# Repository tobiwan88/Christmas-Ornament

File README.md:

# TREE-01 — Wireless RGB Christmas Tree Ornament

**TREE-01** is a double-sided, battery-powered Bluetooth LE Christmas tree ornament built from two stacked 4-layer matte-black & ENIG-gold PCBs. Designed in KiCad 10 with automated geometry, DRC, EMI, and BOM/fab verification.

---

## Highlights

- **Double-Sided 16-LED RGB Matrix:** 16× tiny `1.0 × 1.0 mm` common-anode RGB LEDs (`XL-1010RGB-YG`) — 8 on the front (Board B) and 8 mirrored on the back (Board A) — charlieplexed across just 8 GPIO lines with ghost-free slot scheduling.
- **Ultra-Low-Power BLE SoC:** Nordic `nRF54L10` (QFN-48, pin-compatible with `nRF54L15`) with a `2.45 GHz` Johanson chip antenna at the copper-free tree tip for phone-based time sync, effect selection, and BLE DFU.
- **Smart Power Architecture:** `TPS63900` buck-boost regulator switches between **3.0 V** in sleep (`< 5 µA` whole-board target) and **3.5 V** while LEDs are lit, delivering **~36 days** of runtime (11 h/day schedule) on 2× AAA alkaline cells.
- **Two Power Variants, One PCB:**
  - **Variant A (default):** JLC-assembled SMT 2× AAA holder (`BH-AAA-B5AA001`) centered in the 12 mm inter-board gap.
  - **Variant B:** Rechargeable Li-ion pouch cell with `MCP73831` charger and USB-C power input.
- **Clean 12 mm Sandwich Stack:** Two 1.0 mm boards joined by a single mated 2×4 `2.54 mm` SMD header (8 LED lines) and two `12.0 mm` M2 brass hex standoffs (carrying GND to Board B) with black nylon screws.

---

## Specifications

| Parameter | Value |
|---|---|
| **Dimensions** | `70 × 105 mm` outline, `14.0 mm` board-to-board (`14.8 mm` over LEDs) |
| **PCB Stackup** | 4-layer, `1.0 mm` (`JLC04101H-7628`), matte black solder mask, ENIG gold |
| **MCU & RF** | `nRF54L10-QFAA` (BLE 2.4 GHz), Johanson `2450AT42A100E` chip antenna |
| **LEDs** | 16× `XL-1010RGB-YG` (`1 × 1 × 0.4 mm`), 48 dies charlieplexed on 8 lines |
| **Power** | `TPS63900` buck-boost (`3.0 V` idle / `3.5 V` lit), reverse-polarity P-FET (`Q1`) |
| **Battery** | Variant A: 2× AAA in series (`~36 days` @ 1.0 mA default) · Variant B: Li-ion + USB-C |
| **Controls & Debug** | Rear tactile switch `SW1` (wake / effect / pair), Tag-Connect `TC2030-NL` SWD pads |
| **Panelization** | Single customer panel (`114.8 × 120.0 mm`) nesting Board A and Board B |

---

## Render Gallery

| Front (Board B) | 3/4 View (Inner Board A & Traces) |
|---|---|
|  |  |

| Side Stack (12 mm Gap, AAA Cells & Header) | Back (Board A, SW1 & Tag-Connect) |
|---|---|
|  |  |

---

## Repository Structure

- [`hardware/tree-a/`](hardware/tree-a/) — Main board (SoC, RF, power, battery holder / charger, `D9–D16`, `SW1`, `TC1`)
- [`hardware/tree-b/`](hardware/tree-b/) — Front LED board (`D1–D8`, mated male header `J4`, solid inner GND planes)
- [`hardware/panel/`](hardware/panel/) — Nested 2-board customer panel and [MECHANICAL.md](hardware/panel/MECHANICAL.md)
- [`hardware/ARCHITECTURE.md`](hardware/ARCHITECTURE.md) — Pin plan, charlieplex matrix, and board-to-board interface
- [`hardware/REQUIREMENTS.md`](hardware/REQUIREMENTS.md) — System requirements, power budget, and fab limits
- [`hardware/DECISIONS.md`](hardware/DECISIONS.md) — Engineering decision log (`D1–D37`)
- [`design/`](design/) — V3 design mockups and 3D renders
- [`scripts/`](scripts/) — Automated KiCad DRC, geometry, RF impedance, and BOM/fab verification hooks

---

## License

See [LICENSE](LICENSE).

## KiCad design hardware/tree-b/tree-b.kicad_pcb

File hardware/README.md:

# Hardware: where to look

One row per board. Keep this file current; CLAUDE.md points here instead of naming boards.

| Board | Status | Gate | Notes |
|---|---|---|---|
| tree-a | schematic built and reviewed (3 rounds); routed and frozen, DRC 0 / 0 / 0, parity 0, known exceptions D35 | 5 built; 6 package built, order open | hardware/tree-a/BOARD.md (Routing, Routing review), PARTS-REVIEW.md; owns the order fees |
| tree-b | schematic built and reviewed; routed with KiCadRoutingTools (D31 ground via standoffs), DRC 0 / 0 / 0 | 5 built; 6 via the panel | hardware/tree-b/BOARD.md; fees are paid by tree-a |
| panel | built by gen/panel_pcb.py (114.8 x 120.0 mm, 8 mouse-bite tabs, rails, fiducials), panel-own DRC 0; fab package built (hardware/out/fab/panel) | 6 package built, order open | hardware/panel/BOARD.md, MECHANICAL.md, ORDER.md |

Project documents: REQUIREMENTS.md, ARCHITECTURE.md, DECISIONS.md (D1-D36), NOTES-routing-lessons.md, GATES.md, REVIEW-2026-11-23.md, RESEARCH-2026-11-23.md,
FIRMWARE-RULES.md, ORDER.md (manual PCB + shipping quote, bring-up list). The template board `ornamnents` was retired.

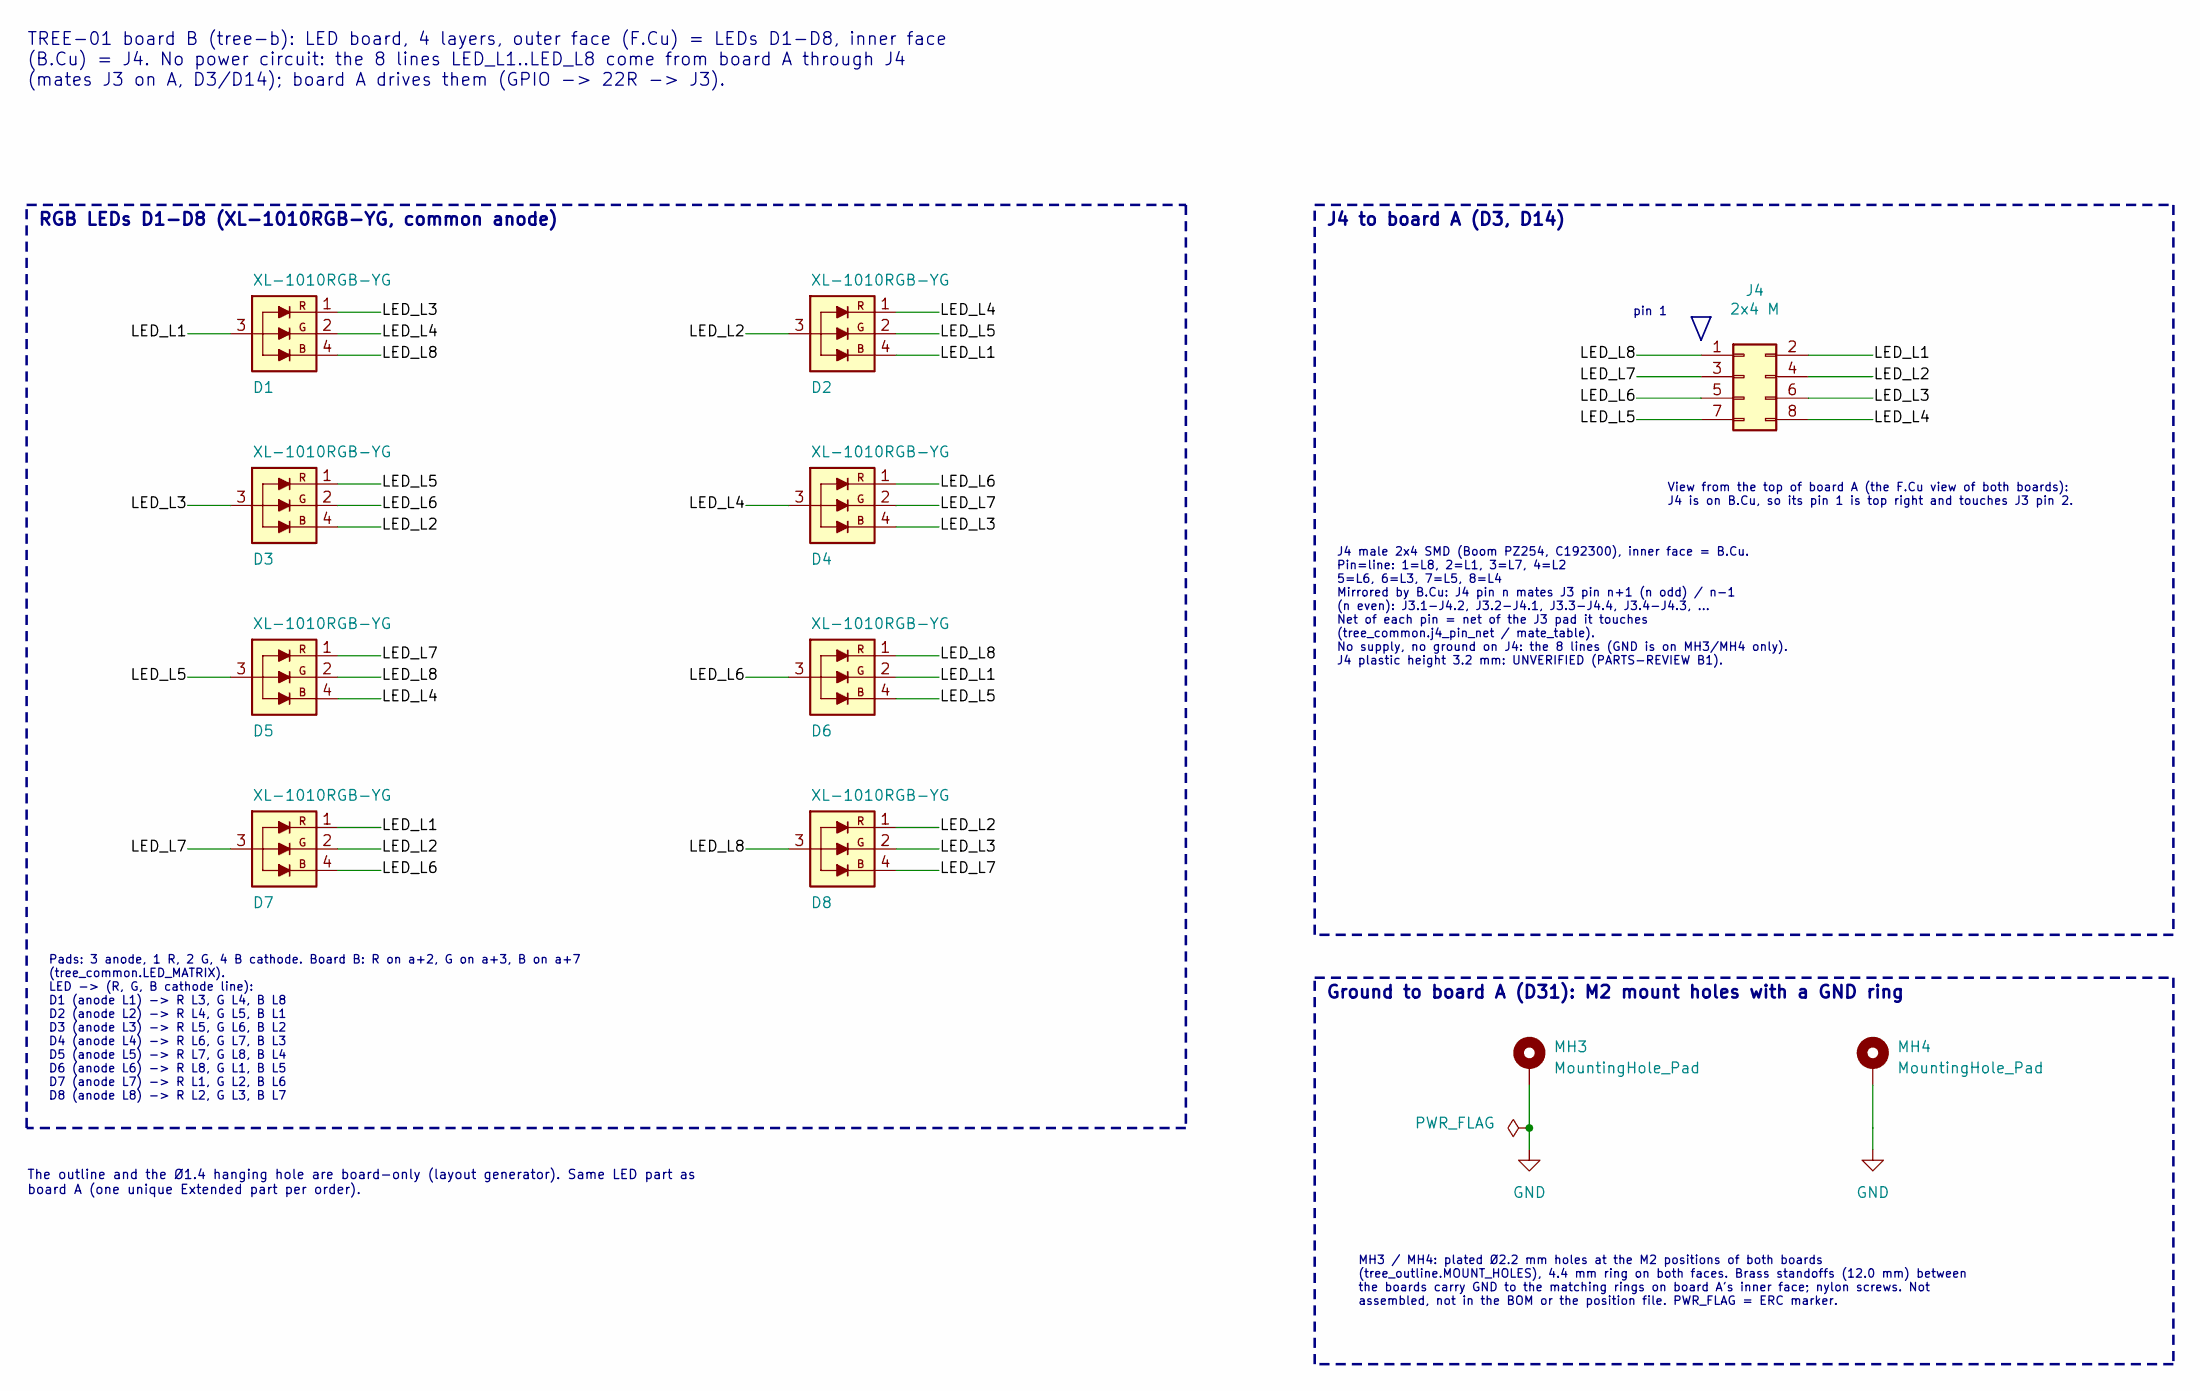
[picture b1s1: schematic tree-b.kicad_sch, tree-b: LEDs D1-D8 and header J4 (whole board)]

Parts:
D1, D2, D3, D4, D5, D6, D7, D8: XL-1010RGB-YG; LED_XL-1010RGB-YG; LCSC C965834
J4: 2x4 M; PinHeader_2x04_SMD_Boom_PZ254; LCSC C192300
MH3, MH4: MountingHole_Pad; MountingHole_2.2mm_M2_Pad

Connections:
/LED_L1: D1.3 (A), D2.4 (BK), D6.2 (GK), D7.1 (RK), J4.2
/LED_L2: D2.3 (A), D3.4 (BK), D7.2 (GK), D8.1 (RK), J4.4
/LED_L3: D1.1 (RK), D3.3 (A), D4.4 (BK), D8.2 (GK), J4.6
/LED_L4: D1.2 (GK), D2.1 (RK), D4.3 (A), D5.4 (BK), J4.8
/LED_L5: D2.2 (GK), D3.1 (RK), D5.3 (A), D6.4 (BK), J4.7
/LED_L6: D3.2 (GK), D4.1 (RK), D6.3 (A), D7.4 (BK), J4.5
/LED_L7: D4.2 (GK), D5.1 (RK), D7.3 (A), D8.4 (BK), J4.3
/LED_L8: D1.4 (BK), D5.2 (GK), D6.1 (RK), D8.3 (A), J4.1
GND: MH3.1, MH4.1

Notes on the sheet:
TREE-01 board B (tree-b): LED board, 4 layers, outer face (F.Cu) = LEDs D1-D8, inner face (B.Cu) = J4. No power circuit: the 8 lines LED_L1..LED_L8 come from board A through J4 (mates J3 on A, D3/D14); board A drives them (GPIO -> 22R -> J3).
Pads: 3 anode, 1 R, 2 G, 4 B cathode. Board B: R on a+2, G on a+3, B on a+7 (tree_common.LED_MATRIX). LED -> (R, G, B cathode line): D1 (anode L1) -> R L3, G L4, B L8 D2 (anode L2) -> R L4, G L5, B L1 D3 (anode L3) -> R L5, G L6, B L2 D4 (anode L4) -> R L6, G L7, B L3 D5 (anode L5) -> R L7, G L8, B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
The outline and the Ø1.4 hanging hole are board-only (layout generator). Same LED part as board A (one unique Extended part per order).
RGB LEDs D1-D8 (XL-1010RGB-YG, common anode)
J4 to board A (D3, D14)
MH3 / MH4: plated Ø2.2 mm holes at the M2 positions of both boards (tree_outline.MOUNT_HOLES), 4.4 mm ring on both faces. Brass standoffs (12.0 mm) between the boards carry GND to the matching rings on board A's inner face; nylon screws. Not assembled, not in the BOM or the position file. PWR_FLAG 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
View from the top of board A (the F.Cu view of both boards): J4 is on B.Cu, so its pin 1 is top right and touches J3 pin 2.
Ground to board A (D31): M2 mount holes with a GND ring
pin 1
J4 male 2x4 SMD (Boom PZ254, C192300), inner face = B.Cu. Pin=line: 1=L8, 2=L1, 3=L7, 4=L2 5=L6, 6=L3, 7=L5, 8=L4 Mirrored by B.Cu: J4 pin n mates J3 pin n+1 (n odd) / n-1 (n even): J3.1-J4.2, J3.2-J4.1, J3.3-J4.4, J3.4-J4.3, ... Net of each pin = net of the J3 pad it touches (tree_common.j4_pin_ne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

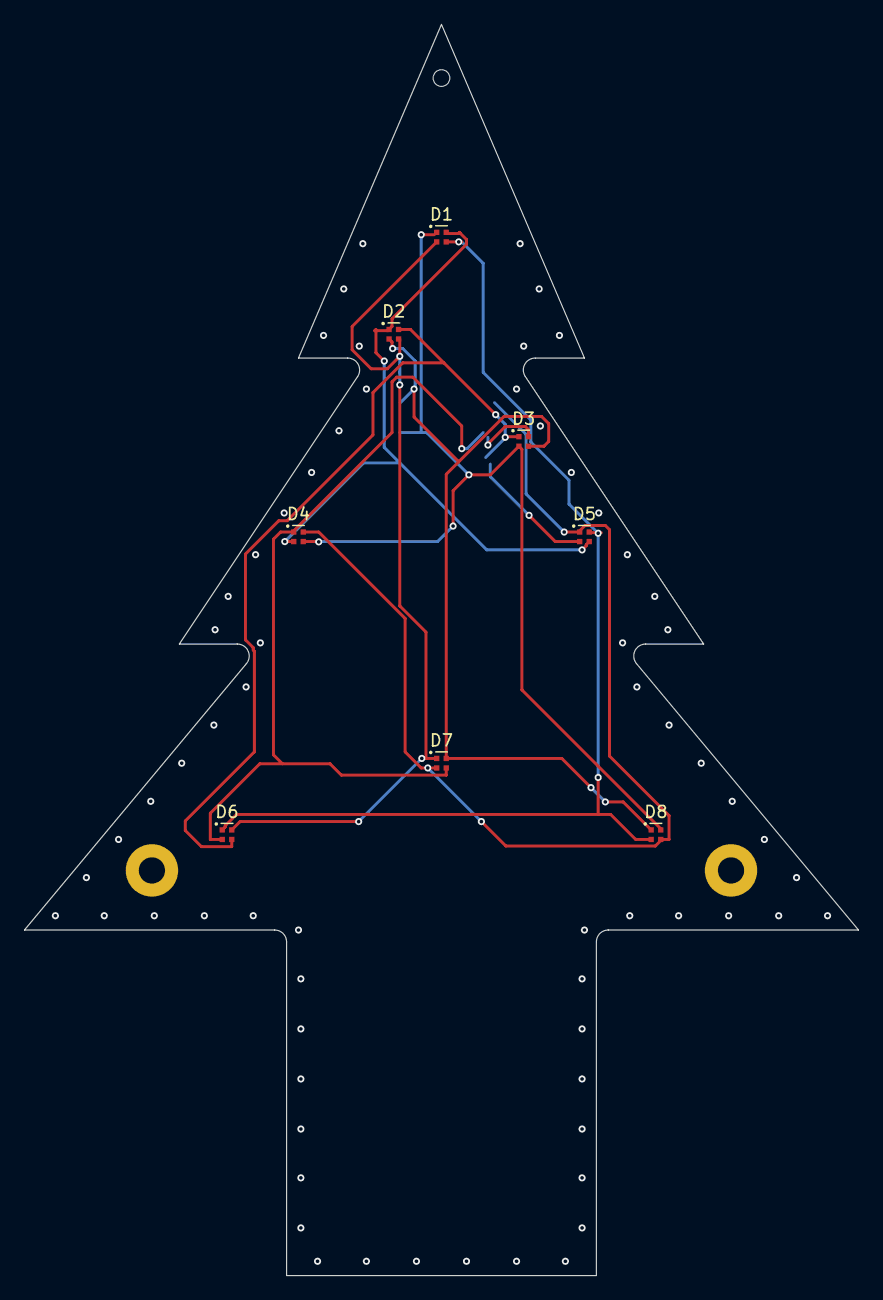
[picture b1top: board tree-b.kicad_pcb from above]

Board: 4 copper layers, 70.0 x 105.0 mm, 12 parts (1 on the bottom side), 9 nets.

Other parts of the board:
H_HANG: NPTH 1.4; MountingHole_1.4mm

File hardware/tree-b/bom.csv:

Comment,Designator,Footprint,Quantity,LCSC Part #,Class,Status,Function / notes
XL-1010RGB-YG (1010),"D1,D2,D3,D4,D5,D6,D7,D8",LED_XL-1010RGB-YG,8,C965834,Extended,"datasheet card, stock 2026-11-23 (PARTS-REVIEW)","RGB LED, outer face (F.Cu of board B)"
2.54-2x4 vertical SMD pin (SMD 2x4 2.54),J4,PinHeader_2x04_SMD_Boom_PZ254,1,C192300,Extended,"datasheet card, stock 2026-11-23 (PARTS-REVIEW)","male header to board A (D3), inner face (B.Cu); mates J3 by position (D14)"

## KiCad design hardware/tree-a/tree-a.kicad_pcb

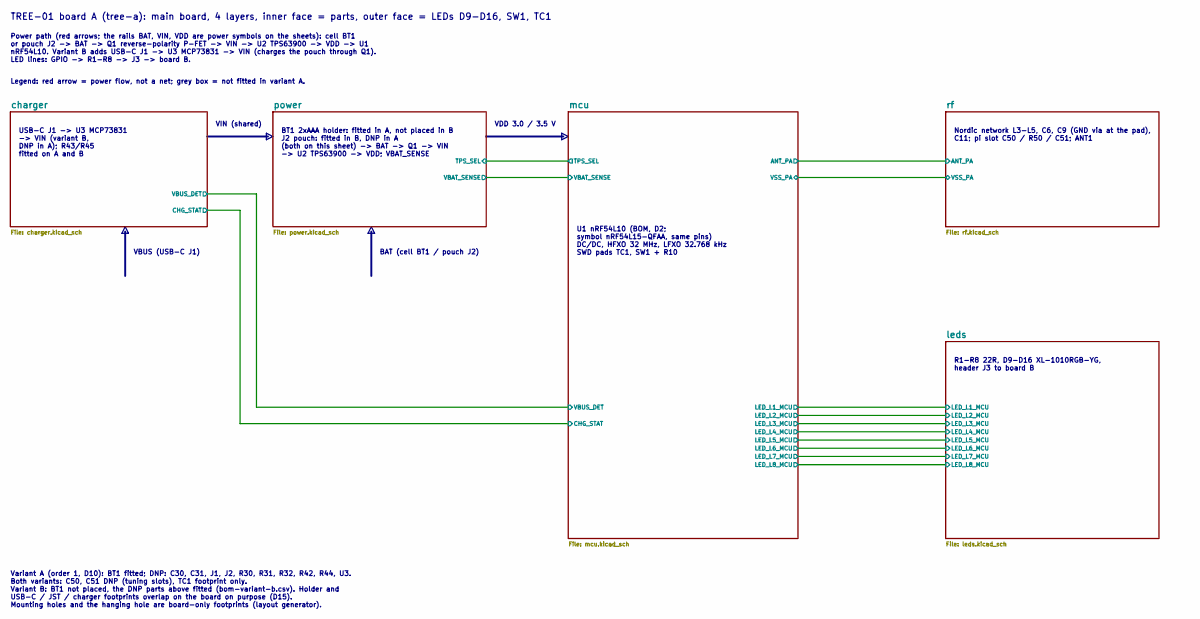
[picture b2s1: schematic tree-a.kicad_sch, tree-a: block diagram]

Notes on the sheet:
BT1 2xAAA holder: fitted in A, not placed in B J2 pouch: fitted in B, DNP in A (both on this sheet) -> BAT -> Q1 -> VIN -> U2 TPS63900 -> VDD; VBAT_SENSE
VBUS (USB-C J1)
VDD 3.0 / 3.5 V
TREE-01 board A (tree-a): main board, 4 layers, inner face = parts, outer face = LEDs D9-D16, SW1, TC1
BAT (cell BT1 / pouch J2)
VIN (shared)
Nordic network L3-L5, C6, C9 (GND via at the pad), C11; pi slot C50 / R50 / C51; ANT1
Variant A (order 1, D10): BT1 fitted; DNP: C30, C31, J1, J2, R30, R31, R32, R42, R44, U3. Both variants: C50, C51 DNP (tuning slots), TC1 footprint only. Variant B: BT1 not placed, the DNP parts above fitted (bom-variant-b.csv). Holder and USB-C / JST / charger footprints overlap on the board on pu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
USB-C J1 -> U3 MCP73831 -> VIN (variant B, DNP in A); R43/R45 fitted on A and B
U1 nRF54L10 (BOM, D2; symbol nRF54L15-QFAA, same pins) DC/DC, HFXO 32 MHz, LFXO 32.768 kHz SWD pads TC1, SW1 + R10
Power path (red arrows; the rails BAT, VIN, VDD are power symbols on the sheets): cell BT1 or pouch J2 -> BAT -> Q1 reverse-polarity P-FET -> VIN -> U2 TPS63900 -> VDD -> U1 nRF54L10. Variant B adds USB-C J1 -> U3 MCP73831 -> VIN (charges the pouch through Q1). LED lines: GPIO -> R1-R8 -> J3 -> boa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
R1-R8 22R, D9-D16 XL-1010RGB-YG, header J3 to board B
Legend: red arrow = power flow, not a net; grey box = not fitted in variant A.

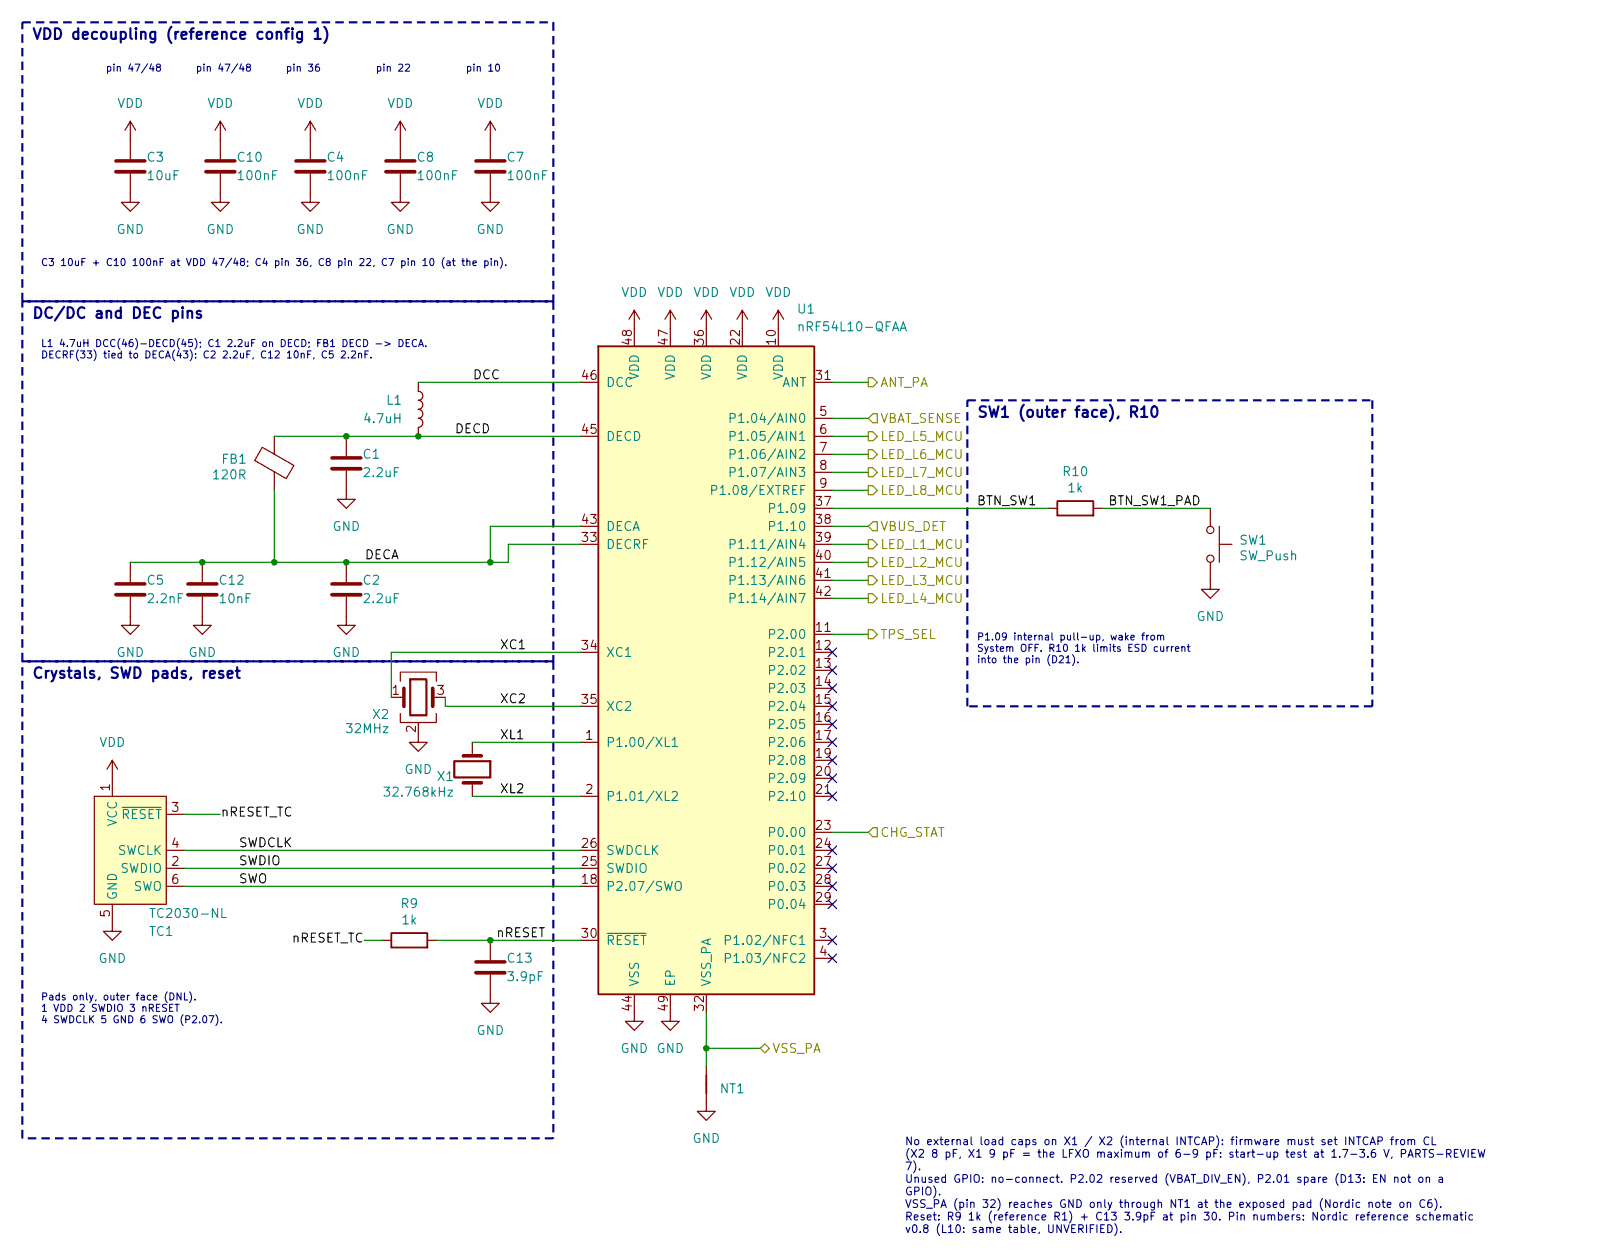
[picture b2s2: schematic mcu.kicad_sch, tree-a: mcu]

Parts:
C1, C2: 2.2uF; C_0402_1005Metric; LCSC C12530
C3: 10uF; C_0402_1005Metric; LCSC C15525
C4, C7, C8, C10: 100nF; C_0402_1005Metric; LCSC C1525
C5: 2.2nF; C_0402_1005Metric; LCSC C1531
C12: 10nF; C_0402_1005Metric; LCSC C15195
C13: 3.9pF; C_0402_1005Metric; LCSC C313081
FB1: 120R; L_0402_1005Metric; LCSC C38480
L1: 4.7uH; L_0805_2012Metric; LCSC C63166
NT1: NetTie; NetTie-2_SMD_Bridge0.2mm
R9, R10: 1k; R_0402_1005Metric; LCSC C11702
SW1: SW_Push; SW_HX_3x4x2-2P-1.6N; LCSC C49234124
TC1: TC2030-NL; Tag-Connect_TC2030-IDC-NL_2x03_P1.27mm_Vertical
U1: nRF54L10-QFAA; QFN-48-1EP_6x6mm_P0.4mm_EP4.66x4.66mm_ThermalVias; LCSC C44800139
X1: 32.768kHz; Crystal_SMD_2012-2Pin_2.0x1.2mm; LCSC C510776
X2: 32MHz; Crystal_SMD_2016-4Pin_2.0x1.6mm; LCSC C2965582

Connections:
/charger/CHG_STAT: U1.23 (P0.00); also elsewhere on the board
/charger/VBUS_DET: U1.38 (P1.10); also elsewhere on the board
/leds/LED_L1_MCU: U1.39 (P1.11/AIN4); also elsewhere on the board
/leds/LED_L2_MCU: U1.40 (P1.12/AIN5); also elsewhere on the board
/leds/LED_L3_MCU: U1.41 (P1.13/AIN6); also elsewhere on the board
/leds/LED_L4_MCU: U1.42 (P1.14/AIN7); also elsewhere on the board
/leds/LED_L5_MCU: U1.6 (P1.05/AIN1); also elsewhere on the board
/leds/LED_L6_MCU: U1.7 (P1.06/AIN2); also elsewhere on the board
/leds/LED_L7_MCU: U1.8 (P1.07/AIN3); also elsewhere on the board
/leds/LED_L8_MCU: U1.9 (P1.08/EXTREF); also elsewhere on the board
/mcu/ANT_PA: U1.31 (ANT); also elsewhere on the board
/mcu/BTN_SW1: R10.1, U1.37 (P1.09)
/mcu/BTN_SW1_PAD: R10.2, SW1.1
/mcu/DCC: L1.1, U1.46 (DCC)
/mcu/DECA: C2.1, C5.1, C12.1, FB1.2, U1.33 (DECRF), U1.43 (DECA)
/mcu/DECD: C1.1, FB1.1, L1.2, U1.45 (DECD)
/mcu/SWDCLK: TC1.4 (SWCLK), U1.26 (SWDCLK)
/mcu/SWDIO: TC1.2 (SWDIO), U1.25 (SWDIO)
/mcu/SWO: TC1.6 (SWO), U1.18 (P2.07/SWO)
/mcu/TPS_SEL: U1.11 (P2.00); also elsewhere on the board
/mcu/VBAT_SENSE: U1.5 (P1.04/AIN0); also elsewhere on the board
/mcu/VSS_PA: NT1.1, U1.32 (VSS_PA); also elsewhere on the board
/mcu/XC1: U1.34 (XC1), X2.1
/mcu/XC2: U1.35 (XC2), X2.3
/mcu/XL1: U1.1 (P1.00/XL1), X1.1
/mcu/XL2: U1.2 (P1.01/XL2), X1.2
/mcu/nRESET: C13.1, R9.2, U1.30 (~RESET)
/mcu/nRESET_TC: R9.1, TC1.3 (~RESET)
GND: C1.2, C2.2, C3.2, C4.2, C5.2, C7.2, C8.2, C10.2, C12.2, C13.2, NT1.2, SW1.2, TC1.5 (GND), U1.44 (VSS), U1.49 (EP), X2.2 (G), X2.4 (G); also elsewhere on the board
VDD: C3.1, C4.1, C7.1, C8.1, C10.1, TC1.1 (VCC), U1.10 (VDD), U1.22 (VDD), U1.36 (VDD), U1.47 (VDD), U1.48 (VDD); also elsewhere on the board

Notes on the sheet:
DC/DC and DEC pins
pin 47/48
Crystals, SWD pads, reset
P1.09 internal pull-up, wake from System OFF. R10 1k limits ESD current into the pin (D21).
L1 4.7uH DCC(46)-DECD(45); C1 2.2uF on DECD; FB1 DECD -> DECA. DECRF(33) tied to DECA(43): C2 2.2uF, C12 10nF, C5 2.2nF.
pin 36
VDD decoupling (reference config 1)
C3 10uF + C10 100nF at VDD 47/48; C4 pin 36, C8 pin 22, C7 pin 10 (at the pin).
pin 22
No external load caps on X1 / X2 (internal INTCAP): firmware must set INTCAP from CL (X2 8 pF, X1 9 pF = the LFXO maximum of 6-9 pF: start-up test at 1.7-3.6 V, PARTS-REVIEW 7). Unused GPIO: no-connect. P2.02 reserved (VBAT_DIV_EN), P2.01 spare (D13: EN not on a GPIO). VSS_PA (pin 32) reaches GND o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
pin 10
Pads only, outer face (DNL). 1 VDD 2 SWDIO 3 nRESET 4 SWDCLK 5 GND 6 SWO (P2.07).
SW1 (outer face), R10

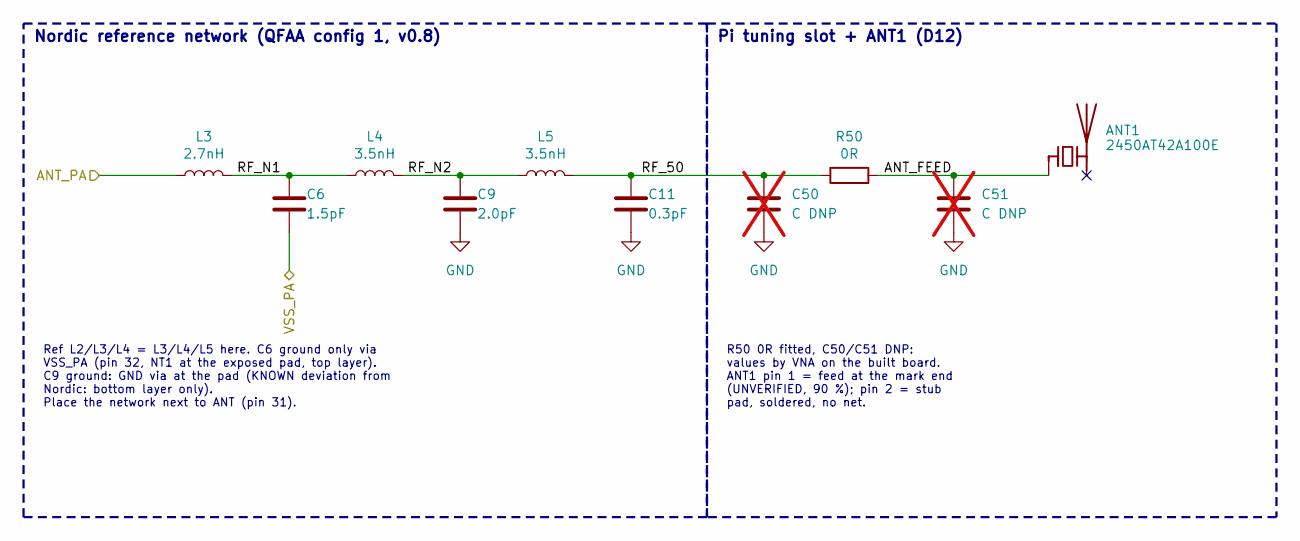
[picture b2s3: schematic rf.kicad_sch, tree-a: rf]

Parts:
ANT1: 2450AT42A100E; ANT_Johanson_2450AT42A100E; LCSC C2917719
C6: 1.5pF; C_0201_0603Metric; LCSC C435397
C9: 2.0pF; C_0201_0603Metric; LCSC C668326
C11: 0.3pF; C_0201_0603Metric; LCSC C161289
C50, C51: C DNP; C_0402_1005Metric; not fitted
L3: 2.7nH; L_0201_0603Metric; LCSC C7216765
L4, L5: 3.5nH; L_0201_0603Metric; LCSC C3911055
R50: 0R; R_0402_1005Metric; LCSC C17168

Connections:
/mcu/ANT_PA: L3.1; also elsewhere on the board
/mcu/VSS_PA: C6.2; also elsewhere on the board
/rf/ANT_FEED: ANT1.1 (FEED), C51.1, R50.2
/rf/RF_50: C11.1, C50.1, L5.2, R50.1
/rf/RF_N1: C6.1, L3.2, L4.1
/rf/RF_N2: C9.1, L4.2, L5.1
GND: C9.2, C11.2, C50.2, C51.2; also elsewhere on the board

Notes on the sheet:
Pi tuning slot + ANT1 (D12)
Ref L2/L3/L4 = L3/L4/L5 here. C6 ground only via VSS_PA (pin 32, NT1 at the exposed pad, top layer). C9 ground: GND via at the pad (KNOWN deviation from Nordic: bottom layer only). Place the network next to ANT (pin 31).
Nordic reference network (QFAA config 1, v0.8)
R50 0R fitted, C50/C51 DNP: values by VNA on the built board. ANT1 pin 1 = feed at the mark end (UNVERIFIED, 90 %); pin 2 = stub pad, soldered, no net.

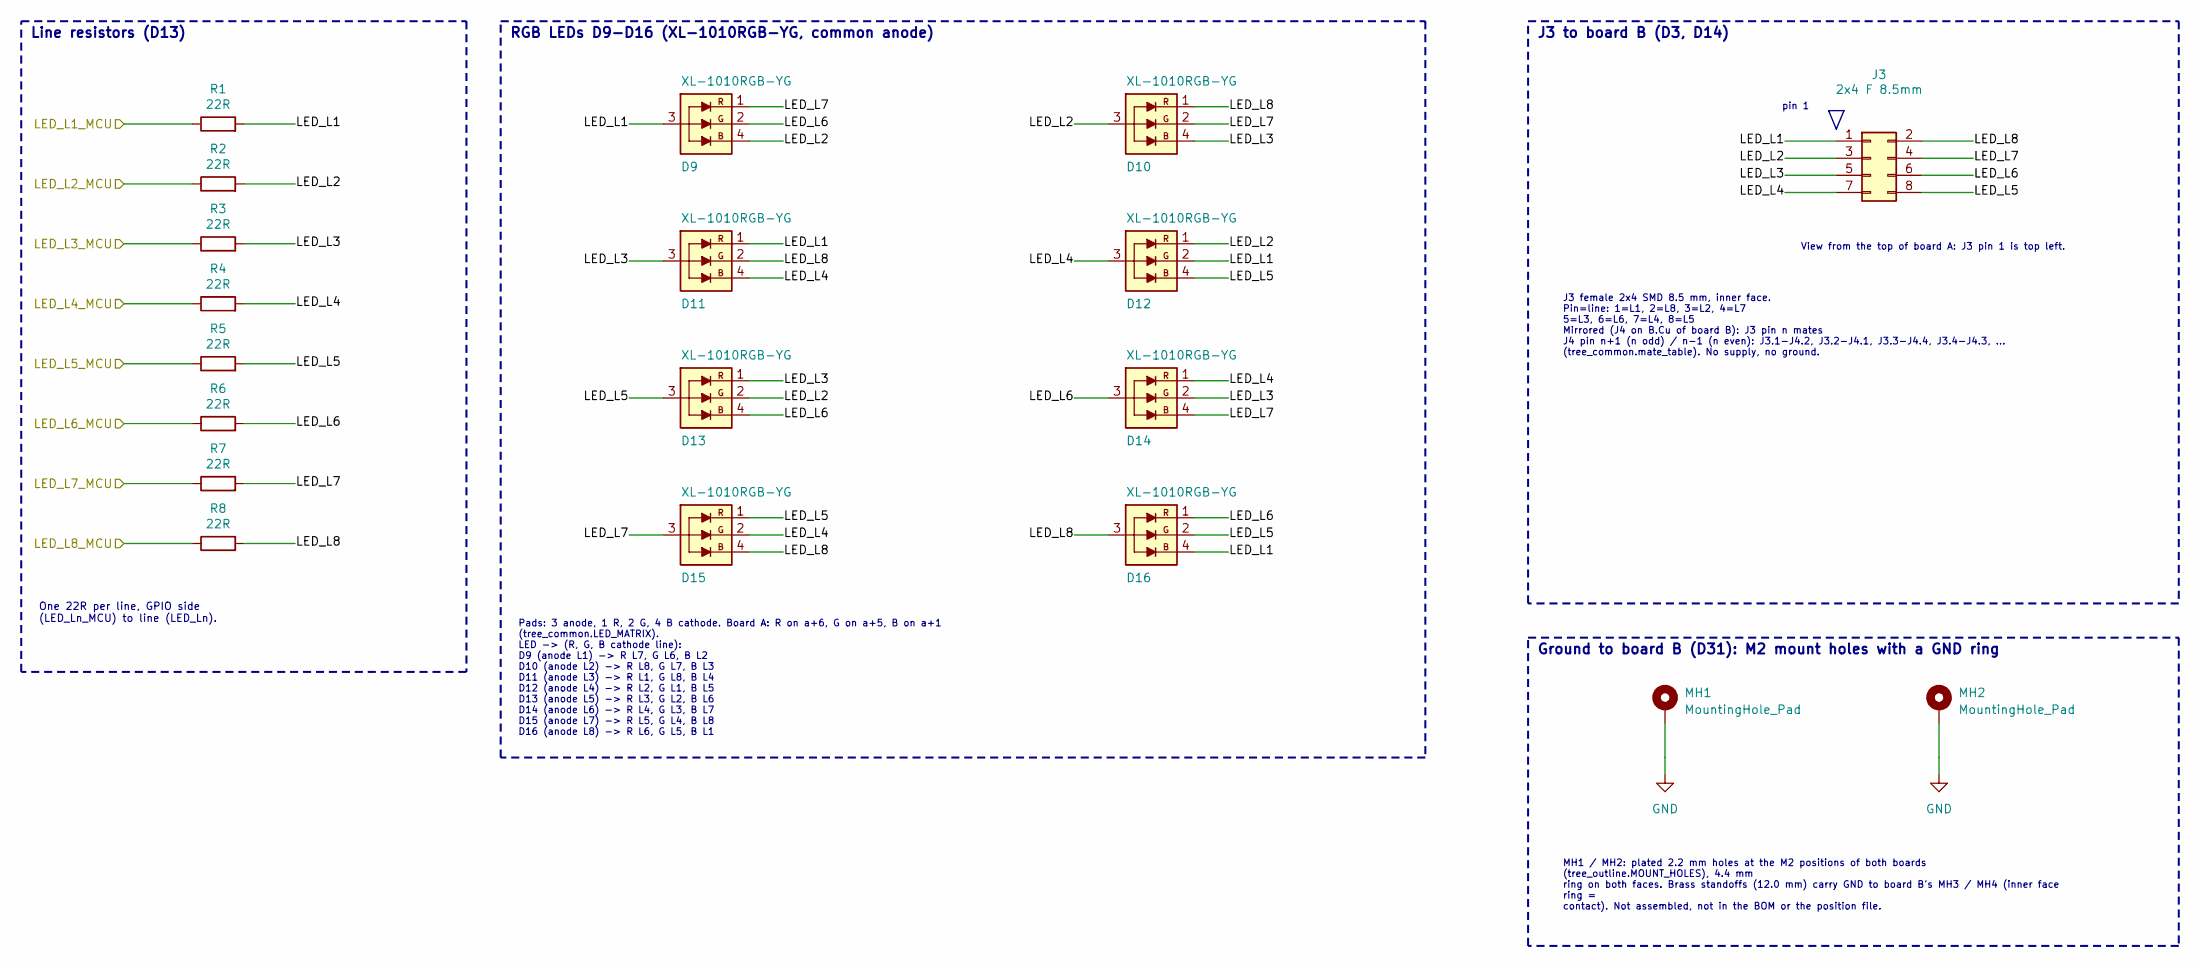
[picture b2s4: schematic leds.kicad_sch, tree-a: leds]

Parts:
D9, D10, D11, D12, D13, D14, D15, D16: XL-1010RGB-YG; LED_XL-1010RGB-YG; LCSC C965834
J3: 2x4 F 8.5mm; PinSocket_2x04_SMD_HC-PM254-8.5H; LCSC C22373945
MH1, MH2: MountingHole_Pad; MountingHole_2.2mm_M2_Pad
R1, R2, R3, R4, R5, R6, R7, R8: 22R; R_0402_1005Metric; LCSC C25092

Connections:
/leds/LED_L1: D9.3 (A), D11.1 (RK), D12.2 (GK), D16.4 (BK), J3.1, R1.2
/leds/LED_L1_MCU: R1.1; also elsewhere on the board
/leds/LED_L2: D9.4 (BK), D10.3 (A), D12.1 (RK), D13.2 (GK), J3.3, R2.2
/leds/LED_L2_MCU: R2.1; also elsewhere on the board
/leds/LED_L3: D10.4 (BK), D11.3 (A), D13.1 (RK), D14.2 (GK), J3.5, R3.2
/leds/LED_L3_MCU: R3.1; also elsewhere on the board
/leds/LED_L4: D11.4 (BK), D12.3 (A), D14.1 (RK), D15.2 (GK), J3.7, R4.2
/leds/LED_L4_MCU: R4.1; also elsewhere on the board
/leds/LED_L5: D12.4 (BK), D13.3 (A), D15.1 (RK), D16.2 (GK), J3.8, R5.2
/leds/LED_L5_MCU: R5.1; also elsewhere on the board
/leds/LED_L6: D9.2 (GK), D13.4 (BK), D14.3 (A), D16.1 (RK), J3.6, R6.2
/leds/LED_L6_MCU: R6.1; also elsewhere on the board
/leds/LED_L7: D9.1 (RK), D10.2 (GK), D14.4 (BK), D15.3 (A), J3.4, R7.2
/leds/LED_L7_MCU: R7.1; also elsewhere on the board
/leds/LED_L8: D10.1 (RK), D11.2 (GK), D15.4 (BK), D16.3 (A), J3.2, R8.2
/leds/LED_L8_MCU: R8.1; also elsewhere on the board
GND: MH1.1, MH2.1; also elsewhere on the board

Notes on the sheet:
MH1 / MH2: plated 2.2 mm holes at the M2 positions of both boards (tree_outline.MOUNT_HOLES), 4.4 mm ring on both faces. Brass standoffs (12.0 mm) carry GND to board B's MH3 / MH4 (inner face ring = contact). Not assembled, not in the BOM or the position file.
RGB LEDs D9-D16 (XL-1010RGB-YG, common anode)
One 22R per line, GPIO side (LED_Ln_MCU) to line (LED_Ln).
View from the top of board A: J3 pin 1 is top left.
Line resistors (D13)
pin 1
Ground to board B (D31): M2 mount holes with a GND ring
J3 to board B (D3, D14)
J3 female 2x4 SMD 8.5 mm, inner face. Pin=line: 1=L1, 2=L8, 3=L2, 4=L7 5=L3, 6=L6, 7=L4, 8=L5 Mirrored (J4 on B.Cu of board B): J3 pin n mates J4 pin n+1 (n odd) / n-1 (n even): J3.1-J4.2, J3.2-J4.1, J3.3-J4.4, J3.4-J4.3, ... (tree_common.mate_table). No supply, no ground.
Pads: 3 anode, 1 R, 2 G, 4 B cathode. Board A: R on a+6, G on a+5, B on a+1 (tree_common.LED_MATRIX). LED -> (R, G, B cathode line): D9 (anode L1) -> R L7, G L6, B L2 D10 (anode L2) -> R L8, G L7, B L3 D11 (anode L3) -> R L1, G L8, B L4 D12 (anode L4) -> R L2, G L1, B L5 D13 (anode L5) -> R L3, G L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

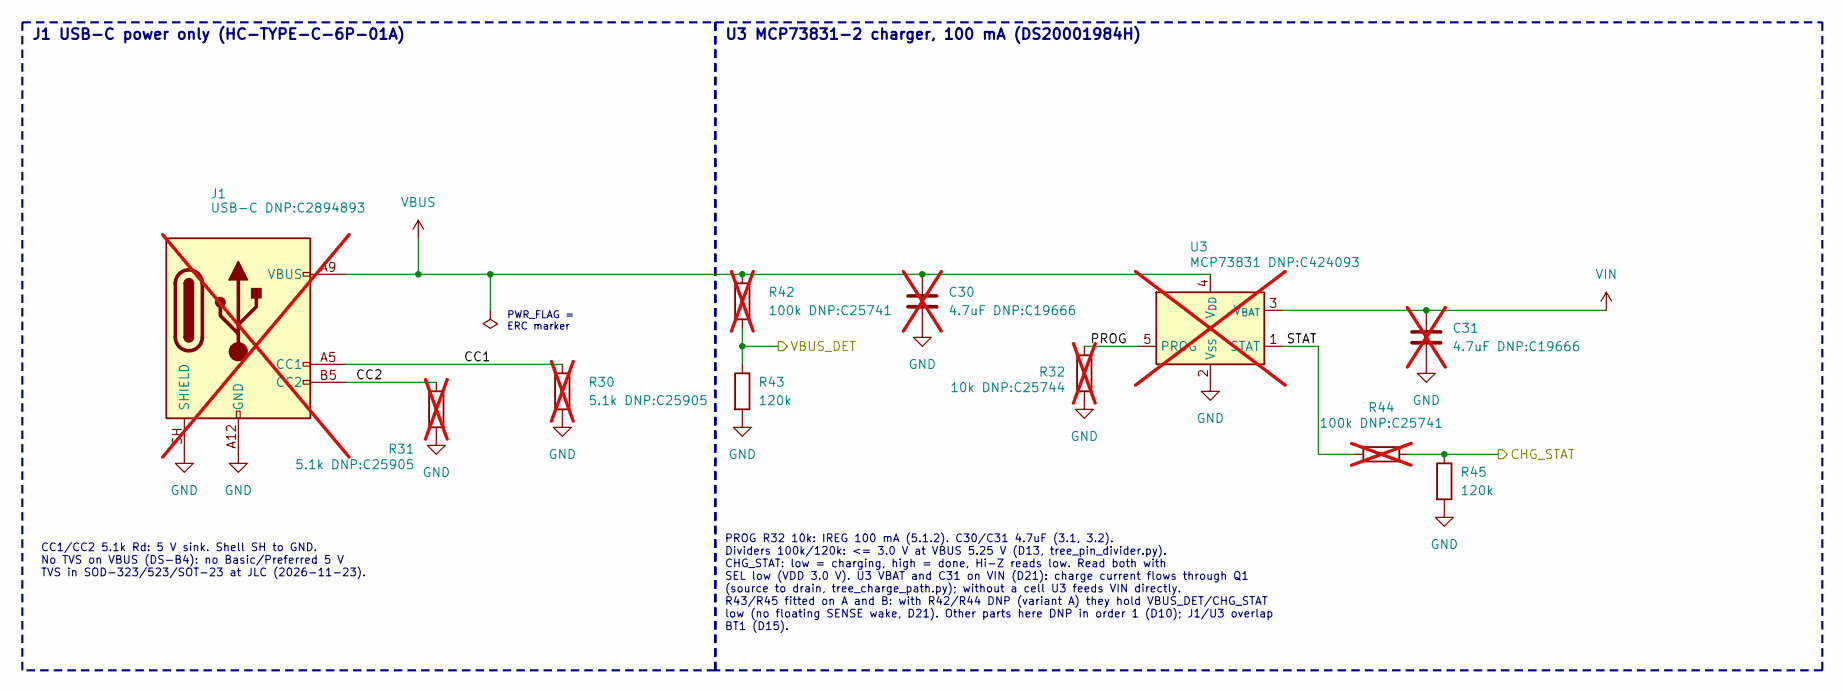
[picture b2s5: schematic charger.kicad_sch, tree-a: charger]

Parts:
C30, C31: 4.7uF DNP:C19666; C_0603_1608Metric; not fitted
J1: USB-C DNP:C2894893; USB_C_HCTL_HC-TYPE-C-6P-01A; not fitted
R30, R31: 5.1k DNP:C25905; R_0402_1005Metric; not fitted
R32: 10k DNP:C25744; R_0402_1005Metric; not fitted
R42, R44: 100k DNP:C25741; R_0402_1005Metric; not fitted
R43, R45: 120k; R_0402_1005Metric; LCSC C25750
U3: MCP73831 DNP:C424093; SOT-23-5; not fitted

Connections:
/charger/CC1: J1.A5 (CC1), R30.1
/charger/CC2: J1.B5 (CC2), R31.1
/charger/CHG_STAT: R44.2, R45.1; also elsewhere on the board
/charger/PROG: R32.1, U3.5 (PROG)
/charger/STAT: R44.1, U3.1 (STAT)
/charger/VBUS_DET: R42.2, R43.1; also elsewhere on the board
GND: C30.2, C31.2, J1.A12 (GND), J1.B12 (GND), J1.SH (SHIELD), R30.2, R31.2, R32.2, R43.2, R45.2, U3.2 (V_{SS}); also elsewhere on the board
VBUS: C30.1, J1.A9 (VBUS), J1.B9 (VBUS), R42.1, U3.4 (V_{DD})
VIN: C31.1, U3.3 (V_{BAT}); also elsewhere on the board

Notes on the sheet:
U3 MCP73831-2 charger, 100 mA (DS20001984H)
CC1/CC2 5.1k Rd: 5 V sink. Shell SH to GND. No TVS on VBUS (DS-B4): no Basic/Preferred 5 V TVS in SOD-323/523/SOT-23 at JLC (2026-11-23).
PROG R32 10k: IREG 100 mA (5.1.2). C30/C31 4.7uF (3.1, 3.2). Dividers 100k/120k: <= 3.0 V at VBUS 5.25 V (D13, tree_pin_divider.py). CHG_STAT: low = charging, high = done, Hi-Z reads low. Read both with SEL low (VDD 3.0 V). U3 VBAT and C31 on VIN (D21): charge current flows through Q1 (source to dr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
J1 USB-C power only (HC-TYPE-C-6P-01A)
PWR_FLAG = ERC marker

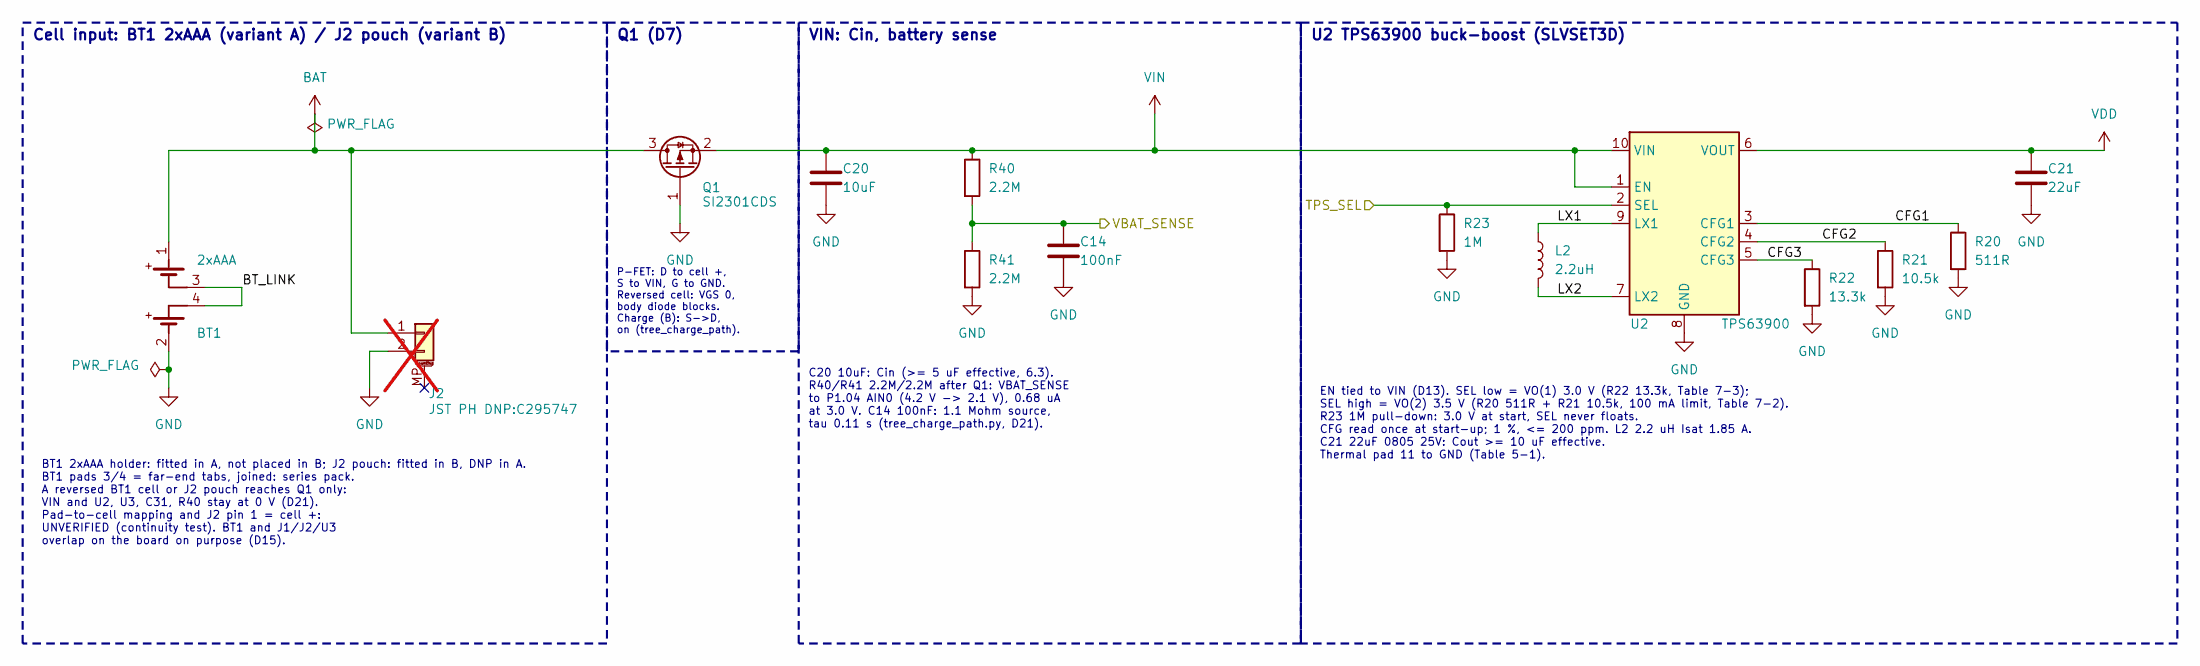
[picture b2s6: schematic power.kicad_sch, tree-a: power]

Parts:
BT1: 2xAAA; BAT_MYOUNG_BH-AAA-B5AA001; LCSC C964881
C14: 100nF; C_0402_1005Metric; LCSC C1525
C20: 10uF; C_0603_1608Metric; LCSC C19702
C21: 22uF; C_0805_2012Metric; LCSC C45783
J2: JST PH DNP:C295747; JST_PH_S2B-PH-SM4-TB_1x02-1MP_P2.00mm_Horizontal; not fitted
L2: 2.2uH; L_Sunlord_SWPA252012S; LCSC C23894
Q1: SI2301CDS; SOT-23; LCSC C10487
R20: 511R; R_0402_1005Metric; LCSC C25124
R21: 10.5k; R_0402_1005Metric; LCSC C25850
R22: 13.3k; R_0402_1005Metric; LCSC C122547
R23: 1M; R_0402_1005Metric; LCSC C26083
R40, R41: 2.2M; R_0402_1005Metric; LCSC C5140754
U2: TPS63900; WSON-10-1EP_2.5x2.5mm_P0.5mm_EP1.2x2mm_ThermalVias; LCSC C1518762

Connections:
/mcu/TPS_SEL: R23.1, U2.2 (SEL); also elsewhere on the board
/mcu/VBAT_SENSE: C14.1, R40.2, R41.1; also elsewhere on the board
/power/BT_LINK: BT1.3 (C1-), BT1.4 (C2+)
/power/CFG1: R20.1, U2.3 (CFG1)
/power/CFG2: R21.1, U2.4 (CFG2)
/power/CFG3: R22.1, U2.5 (CFG3)
/power/LX1: L2.1, U2.9 (LX1)
/power/LX2: L2.2, U2.7 (LX2)
BAT: BT1.1 (+), J2.1, Q1.3 (D)
GND: BT1.2 (-), C14.2, C20.2, C21.2, J2.2, Q1.1 (G), R20.2, R21.2, R22.2, R23.2, R41.2, U2.8 (GND), U2.11 (GND); also elsewhere on the board
VDD: C21.1, U2.6 (VOUT); also elsewhere on the board
VIN: C20.1, Q1.2 (S), R40.1, U2.1 (EN), U2.10 (VIN); also elsewhere on the board

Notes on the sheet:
Cell input: BT1 2xAAA (variant A) / J2 pouch (variant B)
BT1 2xAAA holder: fitted in A, not placed in B; J2 pouch: fitted in B, DNP in A. BT1 pads 3/4 = far-end tabs, joined: series pack. A reversed BT1 cell or J2 pouch reaches Q1 only: VIN and U2, U3, C31, R40 stay at 0 V (D21). Pad-to-cell mapping and J2 pin 1 = cell +: UNVERIFIED (continuity test). BT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
C20 10uF: Cin (>= 5 uF effective, 6.3). R40/R41 2.2M/2.2M after Q1: VBAT_SENSE to P1.04 AIN0 (4.2 V -> 2.1 V), 0.68 uA at 3.0 V. C14 100nF: 1.1 Mohm source, tau 0.11 s (tree_charge_path.py, D21).
P-FET: D to cell +, S to VIN, G to GND. Reversed cell: VGS 0, body diode blocks. Charge (B): S->D, on (tree_charge_path).
EN tied to VIN (D13). SEL low = VO(1) 3.0 V (R22 13.3k, Table 7-3); SEL high = VO(2) 3.5 V (R20 511R + R21 10.5k, 100 mA limit, Table 7-2). R23 1M pull-down: 3.0 V at start, SEL never floats. CFG read once at start-up; 1 %, <= 200 ppm. L2 2.2 uH Isat 1.85 A. C21 22uF 0805 25V: Cout >= 10 uF effecti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
U2 TPS63900 buck-boost (SLVSET3D)
Q1 (D7)
VIN: Cin, battery sense
